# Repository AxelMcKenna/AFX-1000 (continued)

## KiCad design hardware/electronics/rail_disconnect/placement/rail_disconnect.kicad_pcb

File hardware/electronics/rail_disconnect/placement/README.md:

# E25 rail-disconnect placement candidate

Physical continuation of the existing 164-part E17/E21 schematic. This separate directory preserves the circuit snapshot and the verified main-supply PCB.

The proposed 156 × 45.25 × 1.6 mm PCB has six proposed copper layers, fourteen MOSFETs in six opposing banks, six floating gate drivers, the independent OV/reference interlock and all six protected bulk capacitors. Four Ø2.4 mm M2 fixing holes are included. Electrical routing, loss/current distribution, fault timing and thermal performance remain unfinished.

The proposed housing datum is (8,108.5,4.6) mm, in the front strip below the existing controls. This is a placement proposal, not a fit result. The relieved PCB corners clear the existing case bosses. C20/C24 have moved away from the front control supports. A11 adds a local guide/inner-ledge relief for the C24 vent allocation; its separate native CAD report owns the conditional fit result. Header/harness and component heights remain allocations.

Bulk dimensions include the [Panasonic FR-A drawing](https://industrial.panasonic.com/cdbs/www-data/pdf/RDF0000/ABA0000C1259.pdf): D ±0.5 mm, L ±2 mm for the 20/25 mm bodies and L ±1.5 mm for 11.5 mm bodies. A further 0.41 mm seat/board allocation is retained. A11 allocates 2 mm of vent air using the [Panasonic application guidance](https://industrial.panasonic.com/cdbs/www-data/pdf/RDE0000/ABA0000C818.pdf). Physical vent operation and assembly remain unqualified. The driver and MOSFET references remain [Si8751](https://www.skyworksinc.com/-/media/SkyWorks/SL/documents/public/data-sheets/Si8751-2.pdf), [CSD18540Q5B](https://www.ti.com/lit/ds/symlink/csd18540q5b.pdf) and [CSD18510Q5B](https://www.ti.com/lit/ds/symlink/csd18510q5b.pdf). Package grouping is checked; stencil/process, leakage and isolation performance are unqualified.

From the isolated project root:

```sh
python3 -m hardware.electronics.rail_disconnect.placement.generate --kicad-cli /path/to/kicad-cli
python3 -m hardware.electronics.rail_disconnect.placement.check --kicad-cli /path/to/kicad-cli
```

The checker requires original independent circuit/net/value contracts and native all-severity nonrouting DRC/parity, and reports real open connections. It does not suppress routing errors to call this a completed PCB. Rebuilding invalidates old placement evidence. No fabrication or power-up approval follows.

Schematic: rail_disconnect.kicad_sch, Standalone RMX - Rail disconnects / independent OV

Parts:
C1, C5, C9, C13, C17, C21, C25, C29, C34, C35, C36, C37: 100nF 16V X7R; C_0805_2012Metric
C2, C3, C6, C7, C10, C11, C14, C15, C18, C19, C22, C23: 10pF 100V C0G 5%; C_0805_2012Metric
C4, C8: 1500uF 35V electrolytic 20% EEUFR1V152S; CP_Radial_D16.0mm_P7.50mm
C12, C16: 220uF 35V electrolytic 20% EEUFR1V221; CP_Radial_D8.0mm_P3.50mm
C20: 1500uF 16V electrolytic 20% EEUFR1C152; CP_Radial_D10.0mm_P5.00mm
C24: 4700uF 16V electrolytic 20% EEUFR1C472; CP_Radial_D16.0mm_P7.50mm
C26: 1uF 16V X7R; C_0805_2012Metric
C27, C28, C30, C31, C32, C33: 100pF 50V C0G 5%; C_0805_2012Metric
C38: 10uF 16V X7R; C_0805_2012Metric
J1, J3: Header6; PinHeader_1x06_P2.54mm_Vertical
J2, J4: Header2; PinHeader_1x02_P2.54mm_Vertical
J5, J6: Header3; PinHeader_1x03_P2.54mm_Vertical
Q1, Q2, Q3, Q4, Q5, Q6, Q7, Q8: CSD18540Q5B; VSONP-8-1EP_5x6_P1.27mm
Q9, Q10, Q11, Q12, Q13, Q14: CSD18510Q5B; VSONP-8-1EP_5x6_P1.27mm
R1, R9, R17, R25, R33, R41: 22 1%; R_0805_2012Metric
R2, R10, R18, R26, R34, R42, R60, R63, R68, R71, R76, R81, R86, R91: 20M 1%; R_0805_2012Metric
R3, R5, R11, R13, R19, R21, R27, R29, R35, R37, R43, R45, R61, R64, R69, R72, R77, R82, R87, R92: 10k 1%; R_0805_2012Metric
R4, R12, R20, R28, R36, R44: 100 1%; R_0805_2012Metric
R6, R7, R14, R15, R22, R23, R30, R31, R38, R39, R46, R47: 15k 1%; R_0805_2012Metric
R8, R16, R24, R32, R40, R48: 47k 1%; R_0805_2012Metric
R49: 150k 0.01% 5ppm; R_0805_2012Metric
R50: 6.2k 0.01% 5ppm; R_0805_2012Metric
R51, R54, R58, R59, R62, R66, R67, R70, R74, R75, R79, R80, R84, R85, R89, R90, R94: 10k 0.01% 5ppm; R_0805_2012Metric
R52, R55: 1k 1%; R_0805_2012Metric
R53: 100k 0.01% 5ppm; R_0805_2012Metric
R56: 143k 0.01% 5ppm; R_0805_2012Metric
R57: 3.3k 0.01% 5ppm; R_0805_2012Metric
R65: 90.9k 0.01% 5ppm; R_0805_2012Metric
R73, R78: 31.6k 0.01% 5ppm; R_0805_2012Metric
R83: 12.4k 0.01% 5ppm; R_0805_2012Metric
R88: 7.5k 0.01% 5ppm; R_0805_2012Metric
R93: 100k 1%; R_0805_2012Metric
U1, U2, U3, U4, U5, U6: SI8751AB-ISR; SOIC-8_3.9x4.9mm_P1.27mm
U7: REF35125QDBVR; SOT-23-6
U8: OPA2333AID; SOIC-8_3.9x4.9mm_P1.27mm
U9, U10: TLV1824IDR; SOIC-14_3.9x8.7mm_P1.27mm
U11, U12: SN74LVC08APWR; TSSOP-14_4.4x5mm_P0.65mm

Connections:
/5V_DIG: C24.1, J4.1 (5V_DIG), Q12.3 (DRAIN_GROUP), Q14.3 (DRAIN_GROUP), R47.1, R48.1
/5V_DIG_ALLOW: R44.2, R45.1, U6.3 (IN)
/5V_DIG_COMMON: Q11.1 (SOURCE_GROUP), Q12.1 (SOURCE_GROUP), Q13.1 (SOURCE_GROUP), Q14.1 (SOURCE_GROUP), R42.2, U6.5 (SOURCE)
/5V_DIG_DRIVE: R41.1, U6.8 (GATE)
/5V_DIG_GATE: Q11.2 (GATE_GROUP), Q12.2 (GATE_GROUP), Q13.2 (GATE_GROUP), Q14.2 (GATE_GROUP), R41.2, R42.1
/5V_DIG_MCAP1: C22.2, U6.7 (MCAP1)
/5V_DIG_MCAP1_LIMIT: C22.1, R46.2
/5V_DIG_MCAP2: C23.2, U6.6 (MCAP2)
/5V_DIG_MCAP2_LIMIT: C23.1, R47.2
/5V_DIG_OV_OK: R81.1, R82.2, U10.1 (2OUT), U11.10 (3B)
/5V_DIG_OV_REF: R80.2, R81.2, U10.7 (2+)
/5V_DIG_OV_SENSE: C33.1, R78.2, R79.1, U10.6 (2-)
/5V_DIG_SRC: J2.1 (5V_DIG_SRC), Q11.3 (DRAIN_GROUP), Q13.3 (DRAIN_GROUP), R46.1, R78.1
/5V_DIG_TT: R43.1, U6.2 (TT)
/AGND: C1.2, C4.2, C5.2, C8.1, C9.2, C12.2, C13.2, C16.1, C17.2, C20.2, C21.2, C24.2, C25.2, C26.2, C27.2, C28.2, C29.2, C30.2, C31.2, C32.2, C33.2, C34.2, C35.2, C36.2, C37.2, C38.2, J1.2 (AGND), J2.2 (AGND), J3.2 (AGND), J4.2 (AGND), J5.2 (AGND), J6.1 (AGND), R3.2, R5.2, R8.2, R11.2, R13.2, R16.2, R19.2, R21.2, R24.2, R27.2, R29.2, R32.2, R35.2, R37.2, R40.2, R43.2, R45.2, R48.2, R58.2, R66.2, R74.2, R79.2, R84.2, R89.2, R93.2, R94.2, U1.4 (GND), U2.4 (GND), U3.4 (GND), U4.4 (GND), U5.4 (GND), U6.4 (GND), U7.1 (GND), U7.2 (GND), U8.3 (IN+_A), U8.4 (V-), U8.5 (IN+_B), U9.12 (V-), U10.12 (V-), U11.7 (GND), U12.7 (GND)
/ALL_RAILS_ALLOW: J6.2 (ALL_RAILS_ALLOW), R4.1, R12.1, R20.1, R28.1, R36.1, R44.1, U12.11 (4Y)
/N12: C16.2, J3.5 (N12), Q8.3 (DRAIN_GROUP), R31.1, R32.1
/N12_ALLOW: R28.2, R29.1, U4.3 (IN)
/N12_COMMON: Q7.1 (SOURCE_GROUP), Q8.1 (SOURCE_GROUP), R26.2, U4.5 (SOURCE)
/N12_DRIVE: R25.1, U4.8 (GATE)
/N12_GATE: Q7.2 (GATE_GROUP), Q8.2 (GATE_GROUP), R25.2, R26.1
/N12_INV: R54.1, R55.1, U8.7 (OUT_B)
/N12_MCAP1: C14.2, U4.7 (MCAP1)
/N12_MCAP1_LIMIT: C14.1, R30.2
/N12_MCAP2: C15.2, U4.6 (MCAP2)
/N12_MCAP2_LIMIT: C15.1, R31.2
/N12_OV_OK: R71.1, R72.2, U9.13 (4OUT), U11.5 (2B)
/N12_OV_REF: R70.2, R71.2, U9.11 (4+)
/N12_OV_SENSE: C28.1, R55.2, U9.10 (4-)
/N12_SRC: J1.5 (N12_SRC), Q7.3 (DRAIN_GROUP), R30.1, R53.1
/N12_SUM: R53.2, R54.2, U8.6 (IN-_B)
/N12_TT: R27.1, U4.2 (TT)
/N19: C8.2, J3.3 (N19), Q4.3 (DRAIN_GROUP), R15.1, R16.1
/N19_ALLOW: R12.2, R13.1, U2.3 (IN)
/N19_COMMON: Q3.1 (SOURCE_GROUP), Q4.1 (SOURCE_GROUP), R10.2, U2.5 (SOURCE)
/N19_DRIVE: R9.1, U2.8 (GATE)
/N19_GATE: Q3.2 (GATE_GROUP), Q4.2 (GATE_GROUP), R9.2, R10.1
/N19_INPUT_MID: R49.2, R50.1
/N19_INV: R51.1, R52.1, U8.1 (OUT_A)
/N19_MCAP1: C6.2, U2.7 (MCAP1)
/N19_MCAP1_LIMIT: C6.1, R14.2
/N19_MCAP2: C7.2, U2.6 (MCAP2)
/N19_MCAP2_LIMIT: C7.1, R15.2
/N19_OV_OK: R63.1, R64.2, U9.1 (2OUT), U11.2 (1B)
/N19_OV_REF: R62.2, R63.2, U9.7 (2+)
/N19_OV_SENSE: C27.1, R52.2, U9.6 (2-)
/N19_SRC: J1.3 (N19_SRC), Q3.3 (DRAIN_GROUP), R14.1, R49.1
/N19_SUM: R50.2, R51.2, U8.2 (IN-_A)
/N19_TT: R11.1, U2.2 (TT)
/OK_5: U11.8 (3Y), U12.4 (2A)
/OK_12: U11.6 (2Y), U12.2 (1B)
/OK_19: U11.3 (1Y), U12.1 (1A)
/OK_ALL_OV: U12.8 (3Y), U12.12 (4A)
/OK_ANALOG: U12.3 (1Y), U12.9 (3A)
/OK_AUXILIARY: U12.6 (2Y), U12.10 (3B)
/OK_REF: U11.11 (4Y), U12.5 (2B)
/P12: C12.1, J3.4 (P12), Q6.3 (DRAIN_GROUP), R23.1, R24.1
/P12_ALLOW: R20.2, R21.1, U3.3 (IN)
/P12_COMMON: Q5.1 (SOURCE_GROUP), Q6.1 (SOURCE_GROUP), R18.2, U3.5 (SOURCE)
/P12_DRIVE: R17.1, U3.8 (GATE)
/P12_GATE: Q5.2 (GATE_GROUP), Q6.2 (GATE_GROUP), R17.2, R18.1
/P12_MCAP1: C10.2, U3.7 (MCAP1)
/P12_MCAP1_LIMIT: C10.1, R22.2
/P12_MCAP2: C11.2, U3.6 (MCAP2)
/P12_MCAP2_LIMIT: C11.1, R23.2
/P12_OV_OK: R68.1, R69.2, U9.14 (3OUT), U11.4 (2A)
/P12_OV_REF: R67.2, R68.2, U9.9 (3+)
/P12_OV_SENSE: C31.1, R65.2, R66.1, U9.8 (3-)
/P12_SRC: J1.4 (P12_SRC), Q5.3 (DRAIN_GROUP), R22.1, R65.1
/P12_TT: R19.1, U3.2 (TT)
/P19: C4.1, J3.1 (P19), Q2.3 (DRAIN_GROUP), R7.1, R8.1
/P19_ALLOW: R4.2, R5.1, U1.3 (IN)
/P19_COMMON: Q1.1 (SOURCE_GROUP), Q2.1 (SOURCE_GROUP), R2.2, U1.5 (SOURCE)
/P19_DRIVE: R1.1, U1.8 (GATE)
/P19_GATE: Q1.2 (GATE_GROUP), Q2.2 (GATE_GROUP), R1.2, R2.1
/P19_MCAP1: C2.2, U1.7 (MCAP1)
/P19_MCAP1_LIMIT: C2.1, R6.2
/P19_MCAP2: C3.2, U1.6 (MCAP2)
/P19_MCAP2_LIMIT: C3.1, R7.2
/P19_OV_OK: R60.1, R61.2, U9.2 (1OUT), U11.1 (1A)
/P19_OV_REF: R59.2, R60.2, U9.5 (1+)
/P19_OV_SENSE: C30.1, R57.2, R58.1, U9.4 (1-)
/P19_SENSE_MID: R56.2, R57.1
/P19_SRC: J1.1 (P19_SRC), Q1.3 (DRAIN_GROUP), R6.1, R56.1
/P19_TT: R3.1, U1.2 (TT)
/POWER_RUN: J5.3 (POWER_RUN), R93.1, U12.13 (4B)
/PROTECT_REF: C26.1, J6.3 (PROTECT_REF), R59.1, R62.1, R67.1, R70.1, R75.1, R80.1, R85.1, R94.1, U7.6 (VREF), U10.10 (4-)
/REF_HIGH_AUX: R88.2, R89.1, R90.1
/REF_HIGH_OK: R91.1, R92.2, U10.13 (4OUT), U11.13 (4B)
/REF_HIGH_POSITIVE: R90.2, R91.2, U10.11 (4+)
/REF_LOW_AUX: R83.2, R84.1, U10.8 (3-)
/REF_LOW_OK: R86.1, R87.2, U10.14 (3OUT), U11.12 (4A)
/REF_LOW_POSITIVE: R85.2, R86.2, U10.9 (3+)
/V2V5_AUX: C1.1, C5.1, C9.1, C13.1, C17.1, C21.1, C25.1, C29.1, C34.1, C35.1, C36.1, C37.1, C38.1, J5.1 (V2V5_AUX), R61.1, R64.1, R69.1, R72.1, R77.1, R82.1, R83.1, R87.1, R88.1, R92.1, U1.1 (VDD), U2.1 (VDD), U3.1 (VDD), U4.1 (VDD), U5.1 (VDD), U6.1 (VDD), U7.3 (EN), U7.4 (VIN), U8.8 (V+), U9.3 (V+), U10.3 (V+), U11.14 (VCC), U12.14 (VCC)
/V5_REG: C20.1, J3.6 (V5_REG), Q10.3 (DRAIN_GROUP), R39.1, R40.1
/V5_REG_ALLOW: R36.2, R37.1, U5.3 (IN)
/V5_REG_COMMON: Q9.1 (SOURCE_GROUP), Q10.1 (SOURCE_GROUP), R34.2, U5.5 (SOURCE)
/V5_REG_DRIVE: R33.1, U5.8 (GATE)
/V5_REG_GATE: Q9.2 (GATE_GROUP), Q10.2 (GATE_GROUP), R33.2, R34.1
/V5_REG_MCAP1: C18.2, U5.7 (MCAP1)
/V5_REG_MCAP1_LIMIT: C18.1, R38.2
/V5_REG_MCAP2: C19.2, U5.6 (MCAP2)
/V5_REG_MCAP2_LIMIT: C19.1, R39.2
/V5_REG_OV_OK: R76.1, R77.2, U10.2 (1OUT), U11.9 (3A)
/V5_REG_OV_REF: R75.2, R76.2, U10.5 (1+)
/V5_REG_OV_SENSE: C32.1, R73.2, R74.1, U10.4 (1-)
/V5_REG_SRC: J1.6 (V5_REG_SRC), Q9.3 (DRAIN_GROUP), R38.1, R73.1
/V5_REG_TT: R35.1, U5.2 (TT)

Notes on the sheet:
E17: six common-source FET rail disconnects; AUX-powered precision OV sensing and all-rail interlock. Source rails and protected outputs are distinct nets.
Candidate schematic only. No routed board,complete enclosure fit,manufacturer transient/stability model or physical protection proof.
Any source OV/reference-window fault or POWER_RUN low disables all six drivers. Zero source voltage is allowed during startup; no protected-rail supply dependency.
VSONP grouped pads1=S(physical1..3),2=G(physical4),3=D(physical5..8/EP). Body diodes oppose. Gate/source reference floats with each common node.
Si8751 timing maxima use100pF load. Actual FET charge,bulk capacitors,MCAP currents,inrush,leakage,partial-power and fault-energy limits require qualification.

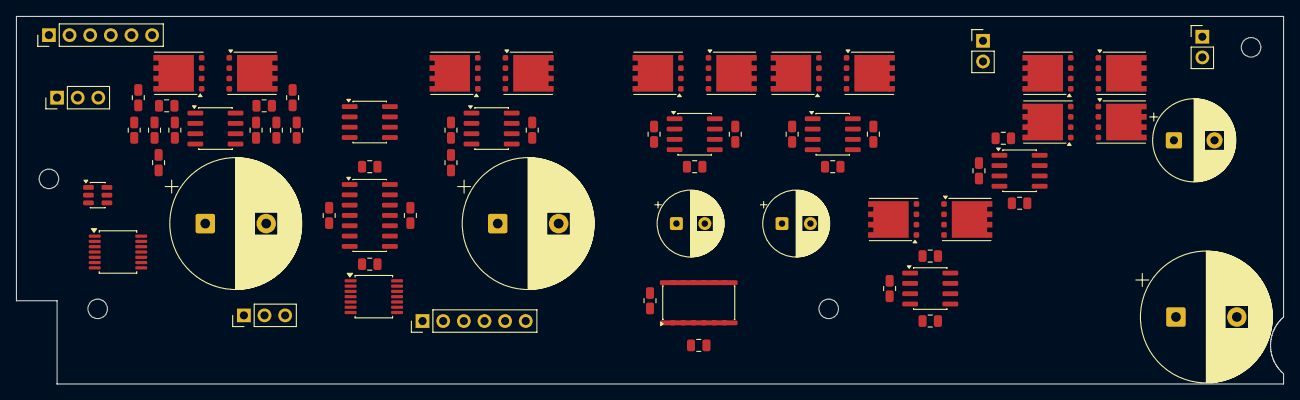
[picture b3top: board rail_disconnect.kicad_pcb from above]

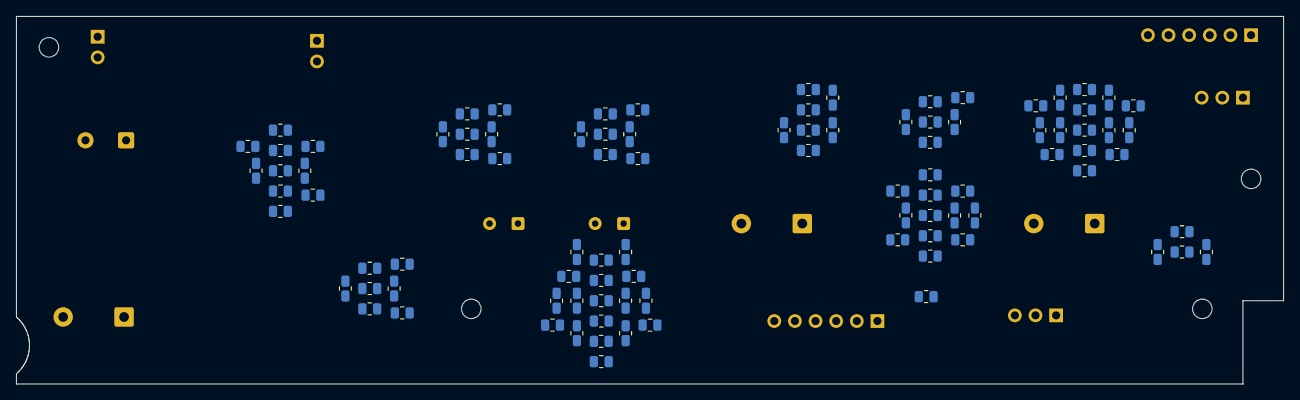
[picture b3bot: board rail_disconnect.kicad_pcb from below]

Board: 6 copper layers, 156.0 x 45.2 mm, 168 parts (94 on the bottom side), 108 nets, no tracks yet.

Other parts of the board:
H1, H2, H3, H4: M2_CLEARANCE; M2_Clearance

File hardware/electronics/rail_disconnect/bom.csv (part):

Reference,Part_or_value,Footprint_candidate,Datasheet,Design_note
Q1,CSD18540Q5B,Package_SON:VSONP-8-1EP_5x6_P1.27mm,https://www.ti.com/lit/ds/symlink/csd18540q5b.pdf,KiCad grouped footprint pads:1=S physical1..3;2=G physical4;3=D physical5..8/exposed drain. Footprint candidate; dimension/stencil approval open.
Q2,CSD18540Q5B,Package_SON:VSONP-8-1EP_5x6_P1.27mm,https://www.ti.com/lit/ds/symlink/csd18540q5b.pdf,KiCad grouped footprint pads:1=S physical1..3;2=G physical4;3=D physical5..8/exposed drain. Footprint candidate; dimension/stencil approval open.
U1,SI8751AB-ISR,Package_SO:SOIC-8_3.9x4.9mm_P1.27mm,https://www.skyworksinc.com/-/media/SkyWorks/SL/documents/pu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,Floating gate power is generated internally. No main-rail startup dependency.35us maximum turn-off uses100pF load and is NOT a bound for these MOSFETs.
R1,22 1%,Resistor_SMD:R_0805_2012Metric,,
R2,20M 1%,Resistor_SMD:R_0805_2012Metric,,Gate leakage budget includes both FETs; do not substitute a low-value gate-source shunt
R3,10k 1%,Resistor_SMD:R_0805_2012Metric,,
R4,100 1%,Resistor_SMD:R_0805_2012Metric,,
R5,10k 1%,Resistor_SMD:R_0805_2012Metric,,Receiving pulldown; missing interlock drive is OFF under10uA input-leakage allocation
C1,100nF 16V X7R,Capacitor_SMD:C_0805_2012Metric,,
R6,15k 1%,Resistor_SMD:R_0805_2012Metric,,Limits step-driven MCAP current; 60V across minimum14.85k is below6mA. Actual clamp sensitivity/dVdt qualification open.
C2,10pF 100V C0G 5%,Capacitor_SMD:C_0805_2012Metric,,Both drain transients monitored; no blanket surge/dVdt approval
R7,15k 1%,Resistor_SMD:R_0805_2012Metric,,Limits step-driven MCAP current; 60V across minimum14.85k is below6mA. Actual clamp sensitivity/dVdt qualification open.
C3,10pF 100V C0G 5%,Capacitor_SMD:C_0805_2012Metric,,Both drain transients monitored; no blanket surge/dVdt approval
C4,1500uF 35V electrolytic 20% EEUFR1V152S,Capacitor_THT:CP_Radial_D16.0mm_P7.50mm,https://industrial.panasonic.com/cdbs/www-data/pdf/RDF0000/A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,"Panasonic FR candidate; nominal D16x20/P7.5 for19V,D16x25/P7.5 digital,D8x11.5/P3.5 for12V,D10x20/P5 analog5V. ESR/ripple/aging,regulator stability,inrush and fit need qualification."
R8,47k 1%,Resistor_SMD:R_0805_2012Metric,,Protected-side bleed is not a rapid discharge or safety-isolation guarantee
Q3,CSD18540Q5B,Package_SON:VSONP-8-1EP_5x6_P1.27mm,https://www.ti.com/lit/ds/symlink/csd18540q5b.pdf,KiCad grouped footprint pads:1=S physical1..3;2=G physical4;3=D physical5..8/exposed drain. Footprint candidate; dimension/stencil approval open.
Q4,CSD18540Q5B,Package_SON:VSONP-8-1EP_5x6_P1.27mm,https://www.ti.com/lit/ds/symlink/csd18540q5b.pdf,KiCad grouped footprint pads:1=S physical1..3;2=G physical4;3=D physical5..8/exposed drain. Footprint candidate; dimension/stencil approval open.
U2,SI8751AB-ISR,Package_SO:SOIC-8_3.9x4.9mm_P1.27mm,https://www.skyworksinc.com/-/media/SkyWorks/SL/documents/pu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,Floating gate power is generated internally. No main-rail startup dependency.35us maximum turn-off uses100pF load and is NOT a bound for these MOSFETs.
R9,22 1%,Resistor_SMD:R_0805_2012Metric,,
R10,20M 1%,Resistor_SMD:R_0805_2012Metric,,Gate leakage budget includes both FETs; do not substitute a low-value gate-source shunt
R11,10k 1%,Resistor_SMD:R_0805_2012Metric,,
R12,100 1%,Resistor_SMD:R_0805_2012Metric,,
R13,10k 1%,Resistor_SMD:R_0805_2012Metric,,Receiving pulldown; missing interlock drive is OFF under10uA input-leakage allocation
C5,100nF 16V X7R,Capacitor_SMD:C_0805_2012Metric,,
R14,15k 1%,Resistor_SMD:R_0805_2012Metric,,Limits step-driven MCAP current; 60V across minimum14.85k is below6mA. Actual clamp sensitivity/dVdt qualification open.
C6,10pF 100V C0G 5%,Capacitor_SMD:C_0805_2012Metric,,Both drain transients monitored; no blanket surge/dVdt approval
R15,15k 1%,Resistor_SMD:R_0805_2012Metric,,Limits step-driven MCAP current; 60V across minimum14.85k is below6mA. Actual clamp sensitivity/dVdt qualification open.
C7,10pF 100V C0G 5%,Capacitor_SMD:C_0805_2012Metric,,Both drain transients monitored; no blanket surge/dVdt approval
C8,1500uF 35V electrolytic 20% EEUFR1V152S,Capacitor_THT:CP_Radial_D16.0mm_P7.50mm,https://industrial.panasonic.com/cdbs/www-data/pdf/RDF0000/A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,"Panasonic FR candidate; nominal D16x20/P7.5 for19V,D16x25/P7.5 digital,D8x11.5/P3.5 for12V,D10x20/P5 analog5V. ESR/ripple/aging,regulator stability,inrush and fit need qualification."
R16,47k 1%,Resistor_SMD:R_0805_2012Metric,,Protected-side bleed is not a rapid discharge or safety-isolation guarantee
Q5,CSD18540Q5B,Package_SON:VSONP-8-1EP_5x6_P1.27mm,https://www.ti.com/lit/ds/symlink/csd18540q5b.pdf,KiCad grouped footprint pads:1=S physical1..3;2=G physical4;3=D physical5..8/exposed drain. Footprint candidate; dimension/stencil approval open.
Q6,CSD18540Q5B,Package_SON:VSONP-8-1EP_5x6_P1.27mm,https://www.ti.com/lit/ds/symlink/csd18540q5b.pdf,KiCad grouped footprint pads:1=S physical1..3;2=G physical4;3=D physical5..8/exposed drain. Footprint candidate; dimension/stencil approval open.
U3,SI8751AB-ISR,Package_SO:SOIC-8_3.9x4.9mm_P1.27mm,https://www.skyworksinc.com/-/media/SkyWorks/SL/documents/pu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,Floating gate power is generated internally. No main-rail startup dependency.35us maximum turn-off uses100pF load and is NOT a bound for these MOSFETs.
R17,22 1%,Resistor_SMD:R_0805_2012Metric,,
R18,20M 1%,Resistor_SMD:R_0805_2012Metric,,Gate leakage budget includes both FETs; do not substitute a low-value gate-source shunt
R19,10k 1%,Resistor_SMD:R_0805_2012Metric,,
R20,100 1%,Resistor_SMD:R_0805_2012Metric,,
R21,10k 1%,Resistor_SMD:R_0805_2012Metric,,Receiving pulldown; missing interlock drive is OFF under10uA input-leakage allocation
C9,100nF 16V X7R,Capacitor_SMD:C_0805_2012Metric,,
R22,15k 1%,Resistor_SMD:R_0805_2012Metric,,Limits step-driven MCAP current; 60V across minimum14.85k is below6mA. Actual clamp sensitivity/dVdt qualification open.
C10,10pF 100V C0G 5%,Capacitor_SMD:C_0805_2012Metric,,Both drain transients monitored; no blanket surge/dVdt approval
R23,15k 1%,Resistor_SMD:R_0805_2012Metric,,Limits step-driven MCAP current; 60V across minimum14.85k is below6mA. Actual clamp sensitivity/dVdt qualification open.
C11,10pF 100V C0G 5%,Capacitor_SMD:C_0805_2012Metric,,Both drain transients monitored; no blanket surge/dVdt approval
C12,220uF 35V electrolytic 20% EEUFR1V221,Capacitor_THT:CP_Radial_D8.0mm_P3.50mm,https://industrial.panasonic.com/cdbs/www-data/pdf/RDF0000/A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,"Panasonic FR candidate; nominal D16x20/P7.5 for19V,D16x25/P7.5 digital,D8x11.5/P3.5 for12V,D10x20/P5 analog5V. ESR/ripple/aging,regulator stability,inrush and fit need qualification."
R24,47k 1%,Resistor_SMD:R_0805_2012Metric,,Protected-side bleed is not a rapid discharge or safety-isolation guarantee
Q7,CSD18540Q5B,Package_SON:VSONP-8-1EP_5x6_P1.27mm,https://www.ti.com/lit/ds/symlink/csd18540q5b.pdf,KiCad grouped footprint pads:1=S physical1..3;2=G physical4;3=D physical5..8/exposed drain. Footprint candidate; dimension/stencil approval open.
Q8,CSD18540Q5B,Package_SON:VSONP-8-1EP_5x6_P1.27mm,https://www.ti.com/lit/ds/symlink/csd18540q5b.pdf,KiCad grouped footprint pads:1=S physical1..3;2=G physical4;3=D physical5..8/exposed drain. Footprint candidate; dimension/stencil approval open.
U4,SI8751AB-ISR,Package_SO:SOIC-8_3.9x4.9mm_P1.27mm,https://www.skyworksinc.com/-/media/SkyWorks/SL/documents/pu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,Floating gate power is generated internally. No main-rail startup dependency.35us maximum turn-off uses100pF load and is NOT a bound for these MOSFETs.
R25,22 1%,Resistor_SMD:R_0805_2012Metric,,
R26,20M 1%,Resistor_SMD:R_0805_2012Metric,,Gate leakage budget includes both FETs; do not substitute a low-value gate-source shunt
R27,10k 1%,Resistor_SMD:R_0805_2012Metric,,
R28,100 1%,Resistor_SMD:R_0805_2012Metric,,
R29,10k 1%,Resistor_SMD:R_0805_2012Metric,,Receiving pulldown; missing interlock drive is OFF under10uA input-leakage allocation
C13,100nF 16V X7R,Capacitor_SMD:C_0805_2012Metric,,
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
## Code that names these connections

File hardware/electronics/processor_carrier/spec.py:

"""E19 external-profile processor carrier and ten pot interfaces."""

from pathlib import Path

ROOT = Path(__file__).resolve().parent
SEED = "https://daisy.nyc3.cdn.digitaloceanspaces.com/products/seed3/Daisy_Seed3_datasheet.pdf"
COMPONENTS = []
KNOBS = [
    "input",
    "output",
    "low",
    "mid",
    "high",
    "scene_depth",
    "x_level",
    "x_pitch",
    "scene_time",
    "scene_resonance",
]


def pin(n, name, kind, net, side="L"):
    return dict(number=str(n), name=name, kind=kind, net=net, side=side)


def part(ref, value, fp, pins, x, y, note="", source=""):
    COMPONENTS.append(
        dict(
            ref=ref,
            part=value,
            footprint=fp,
            pins=pins,
            x=round(round(x / 1.27) * 1.27, 4),
            y=round(round(y / 1.27) * 1.27, 4),
            note=note,
            source=source,
        )
    )


GPIO = [
    "CODEC_RUN",
    "SDMMC_D3_SRC",
    "SDMMC_D2_SRC",
    "SDMMC_D1_SRC",
    "SDMMC_D0_SRC",
    "SDMMC_CMD_SRC",
    "SDMMC_CLK_SRC",
    "LED_XLAT_SRC",
    "LED_SCK_SRC",
    "GAIN_REQ",
    "LED_MOSI_SRC",
    "SCL",
    "SDA",
    "HEARTBEAT",
    "LED_BLANK_SRC",
]
PINS = [
    pin(i + 1, "D" + str(i), "bidirectional" if i in (1, 2, 3, 4, 5, 11, 12) else "output", net)
    for i, net in enumerate(GPIO)
]
PINS += [
    pin(i, name, kind, net, "L")
    for i, name, kind, net in [
        (16, "AUDIO_IN_L", "input", None),
        (17, "AUDIO_IN_R", "input", None),
        (18, "AUDIO_OUT_L", "output", None),
        (19, "AUDIO_OUT_R", "output", None),
        (20, "AGND", "power_in", "AGND"),
    ]
]
PINS += [pin(21, "3V3_ANALOG", "power_out", "V3V3_ANALOG", "R")]
PINS += [pin(22 + i, "D" + str(15 + i), "input", f"POT_ADC_{i:02d}", "R") for i in range(10)]
PINS += [
    pin(i, name, kind, net, "R")
    for i, name, kind, net in [
        (32, "D25_ADC_DATA", "input", "ADC_DATA"),
        (33, "D26_DAC_DATA", "output", "DAC_DATA_SRC"),
        (34, "D27_WS", "input", "WS"),
        (35, "D28_BCLK", "input", "BCLK"),
        (36, "D29_PERMIT", "output", "MCU_PERMIT"),
        (37, "D30_ARMED", "input", "ARMED"),
        (38, "3V3_DIGITAL", "power_out", "V3V3_IO"),
        (39, "VIN", "power_in", "SEED_VIN"),
        (40, "DGND", "power_in", "AGND"),
    ]
]
part(
    "U1",
    "DaisySeed3",
    "RMX_Carrier:Seed3_Socket40",
    PINS,
    95,
    110,
    "External firmware profile only. Carrier assembly includes Seed3 and2xSSW-120-02-G-S sockets; clip socket solder tails<=3mm including solder.",
    SEED,
)


def header(ref, nets, x, y, note=""):
    part(
        ref,
        "Header" + str(len(nets)),
        f"Connector_PinHeader_2.54mm:PinHeader_1x{len(nets):02d}_P2.54mm_Vertical",
        [pin(i + 1, str(i + 1), "passive", net) for i, net in enumerate(nets)],
        x,
        y,
        note,
    )


HEADERS = [
    ("J1", ["5V_DIG", "AGND"], "Protected digital supply from E17 J4, same pin order; no raw12V input."),
    (
        "J2",
        ["AGND", "V3V3_IO", "SCL", "SDA", "CODEC_RUN"],
        "E18 J5; CODEC_RUN alias CONTROL_RESET_N; external profile only.",
    ),
    (
        "J3",
        ["AGND", "HEARTBEAT", "MCU_PERMIT", "GAIN_REQ", "ARMED", "BYPASS_SENSE"],
        "E11 J2 six-pin order; bypass sense passes to E18 rear header.",
    ),
    (
        "J4",
        ["AGND", "MODE_SEND_RETURN", "BYPASS_SENSE", "ANALOG_OK", "INPUT_READY"],
        "E18 J4; BYPASS_SENSE alias MANUAL_BYPASS.",
    ),
    ("J5", ["AGND", "BCLK", "WS", "ADC_DATA", "DAC_DATA"], "E09 J3; DAC_DATA source damping at carrier."),
    (
        "J6",
        ["AGND", "V3V3_IO", "SCL", "SDA", "CODEC_RUN", "ANALOG_OK"],
        "Split harness to E09 J4 IO power/J5 bus/status. Do not join independent3.3V outputs.",
    ),
    ("J7", ["AGND", "INPUT_READY"], "E11 J6 status."),
    ("J8", ["AGND", "MODE_SEND_RETURN"], "Rear maintained CONNECTION contact: closed=send/return."),
    (
        "J9",
        ["AGND", "V3V3_IO", "SCL", "SDA"],
        "Trill Craft bus; include module pull-ups in whole-bus budget.",
    ),
    ("J10", ["AGND", "V3V3_IO", "SCL", "SDA"], "AS5600 board bus; sensor board incomplete."),
    (
        "J11",
        ["AGND", "5V_DIG", "V3V3_IO", "LED_MOSI", "LED_SCK", "LED_XLAT", "LED_BLANK", "AGND"],
        "TLC5947 board interface; receiving BLANK pull-up still required on future LED board.",
    ),
    (
        "J12",
        ["AGND", "V3V3_IO", "SDMMC_D0", "SDMMC_D1", "SDMMC_D2", "SDMMC_D3", "SDMMC_CMD", "SDMMC_CLK"],
        "Reserved SDMMC interface. Card-power budget, socket/detect, filesystem and physical SI unfinished.",
    ),
]
for index, (ref, nets, note) in enumerate(HEADERS):
    header(ref, nets, 235 + 135 * (index % 6), 65 + 100 * (index // 6), note)


def passive(ref, value, a, b, x, y, fp=None, note=""):
    kind = "Resistor" if ref.startswith("R") else "Capacitor"
    part(
        ref,
        value,
        fp or f"{kind}_SMD:{ref[0]}_0805_2012Metric",
        [pin(1, "~", "passive", a), pin(2, "~", "passive", b, "R")],
        x,
        y,
        note,
    )


PULLS = [
    ("R1", "0.47R 1% 1W", "5V_DIG", "SEED_VIN"),
    ("R2", "10k 1%", "LED_BLANK", "V3V3_IO"),
    ("R3", "100k 1%", "MCU_PERMIT", "AGND"),
    ("R4", "100k 1%", "GAIN_REQ", "AGND"),
    ("R5", "100k 1%", "ARMED", "AGND"),
    ("R6", "100k 1%", "CODEC_RUN", "AGND"),
]
SERIES = [
    "LED_XLAT",
    "LED_SCK",
    "LED_MOSI",
    "LED_BLANK",
    "DAC_DATA",
    "SDMMC_D0",
    "SDMMC_D1",
    "SDMMC_D2",
    "SDMMC_D3",
    "SDMMC_CMD",
    "SDMMC_CLK",
]
for i, (ref, value, a, b) in enumerate(PULLS):
    passive(
        ref,
        value,
        a,
        b,
        45 + 95 * i,
        530,
        "Resistor_SMD:R_2512_6332Metric" if ref == "R1" else None,
        "Source resistor budget uses0.5A; physical load, thermal and startup qualification open."
        if ref == "R1"
        else "",
    )
for i, net in enumerate(SERIES):
    passive(
        f"R{10 + i}",
        "33R 1%",
        net + "_SRC",
        net,
        45 + 95 * (i % 10),
        565 + 35 * (i // 10),
        note="Source damping; physical edge/SI qualification unfinished.",
    )
CAPS = [
    ("22uF 25V X7R", "SEED_VIN"),
    ("100nF 16V X7R", "SEED_VIN"),
    ("1uF 16V X7R", "V3V3_ANALOG"),
    ("100nF 16V X7R", "V3V3_ANALOG"),
    ("4.7uF 16V X7R", "V3V3_IO"),
    ("100nF 16V X7R", "V3V3_IO"),
]
for i, (value, rail) in enumerate(CAPS):
    passive(
        f"C{i + 1}",
        value,
        rail,
        "AGND",
        45 + 95 * (i + 1),
        600,
        "Capacitor_SMD:C_1210_3225Metric" if i == 0 else None,
    )
for i, name in enumerate(KNOBS):
    x, y = 245 + 160 * (i % 5), 300 + 100 * (i // 5)
    header(
        f"J{20 + i}",
        ["AGND", f"POT_RAW_{i:02d}", "V3V3_ANALOG"],
        x,
        y,
        f"{name}: 10k linear pot; excitation is module analog3.3V output.",
    )
    passive(f"R{31 + i}", "1k 1%", f"POT_RAW_{i:02d}", f"POT_ADC_{i:02d}", x, y + 32)
    passive(f"C{11 + i}", "100nF 16V X7R", f"POT_ADC_{i:02d}", "AGND", x, y + 62)
    passive(
        f"R{41 + i}",
        "1M 1%",
        f"POT_ADC_{i:02d}",
        "AGND",
        x + 70,
        y + 62,
        note="Open-wiper bleed; does not provide wire-fault detection.",
    )
NOTES = [
    (
        20,
        18,
        "E19 - external-profile Seed3 processor carrier.40 module pins,10 analog pots,control-hub/codec/relay/LED/sensor/SD interfaces.",
    ),
    (
        20,
        28,
        "3.3V outputs are separate: analog pin21 excites pots; digital pin38 powers shared logic. AGND and DGND join on carrier.",
    ),
    (
        20,
        638,
        "Routed150x65mm carrier: front-slot Seed and2mm E18 daughterboard shift implemented in PCB/A05 CAD; physical assembly unverified.",
    ),
    (
        20,
        648,
        "No whole-bus/3.3V load, USB partial-power/backfeed, ADC acquisition/accuracy, SDMMC SI or physical fit approval. No fabrication release.",
    ),
]

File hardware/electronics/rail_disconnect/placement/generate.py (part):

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            return FIXED["U" + str((int(ref[1:]) - 1) // 4 + 1)][:2]
        if ref.startswith("R") and int(ref[1:]) <= 42:
            return FIXED["U" + str((int(ref[1:]) - 1) // 7 + 1)][:2]
        special = set(pins[ref].values()) - {"AGND", "V2V5_AUX", "PROTECT_REF", "ALL_RAILS_ALLOW"}
        ranked = sorted(((-len(special & set(pins[u].values())), u) for u in FIXED if u.startswith("U")))
        return FIXED[ranked[0][1]][:2]

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
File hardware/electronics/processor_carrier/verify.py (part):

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        assert pins["U1"][str(gpio + 1)] == net
    profile = (FIRMWARE / "BoardProfile.h").read_text()
    for variable, gpio, physical, net in [
        ("permitPin", 29, 36, "MCU_PERMIT"),
        ("armedPin", 30, 37, "ARMED"),
        ("resetPin", 0, 1, "CODEC_RUN"),
    ]:
        assert re.search(rf"\b{variable}\s*=\s*externalConverter\s*\?\s*{gpio}\s*:", profile)
        assert pins["U1"][str(physical)] == net
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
